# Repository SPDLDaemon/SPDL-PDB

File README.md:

# Smart Product Design Lab - Power Distribution Board v2.1
## features
* 16 JST XH plugs with 3.3v ground and 5 volts
* 8 molex 254 plugs for servos

## user guide image

#### [link to user guide image](/218PDBguide.drawio.png)

### [link to schematic](/schematic.pdf)
#### [link to image of PCB traces](/pcb.pdf)
<!-- ### board explanation video coming soon -->

## assembly
### [assembly instructions](/assembly_instructions.md)

[Interactive BOM](/ibom.html) (download file and open in a browser)

<!-- ### assembly video coming soon -->

## current limits:
* board total: 16 amps (theoretical) ??? amps (tested), limited by the traces and main battery screw terminals
* 5-3: 2 amps (theoretical) ??? amps (tested), limited by the HW-411 buck voltage regulator
* 3.3-1 + 5-1: 1 amp (theoretical) ??? amps (tested), limited by the TLV761 linear voltage regulator
* 3.3-2 + 5-2: 1 amp (theoretical) ??? amps (tested), limited by the TLV761 linear voltage regulator

## images

## KiCAD Symbols
### [simple symbol](https://github.com/SPDLDaemon/SPDL-PDB/blob/main/pdb.kicad_sym)

### [detailed symbol](https://github.com/SPDLDaemon/SPDL-PDB/blob/main/pdb-detailed.kicad_sym)

## buying PCBs and components 
1x set of components from [bill of materials](/BOM.csv)

2x tamiya connectors for batteries (with wires)

1x main power switch (for example 141-RCA1913F1ABLKBLKWHT3-ND)

1x fuse holder (with wires) and fuse

1x PCB from ([gerber files](/gerbers.zip))

JST XH socket housings (16) 455-2219-ND

JST XH socket crimps (48) 455-1135-1000-ND

4 inches of 18 AWG wire

small flathead screwdriver

JST XH crimper

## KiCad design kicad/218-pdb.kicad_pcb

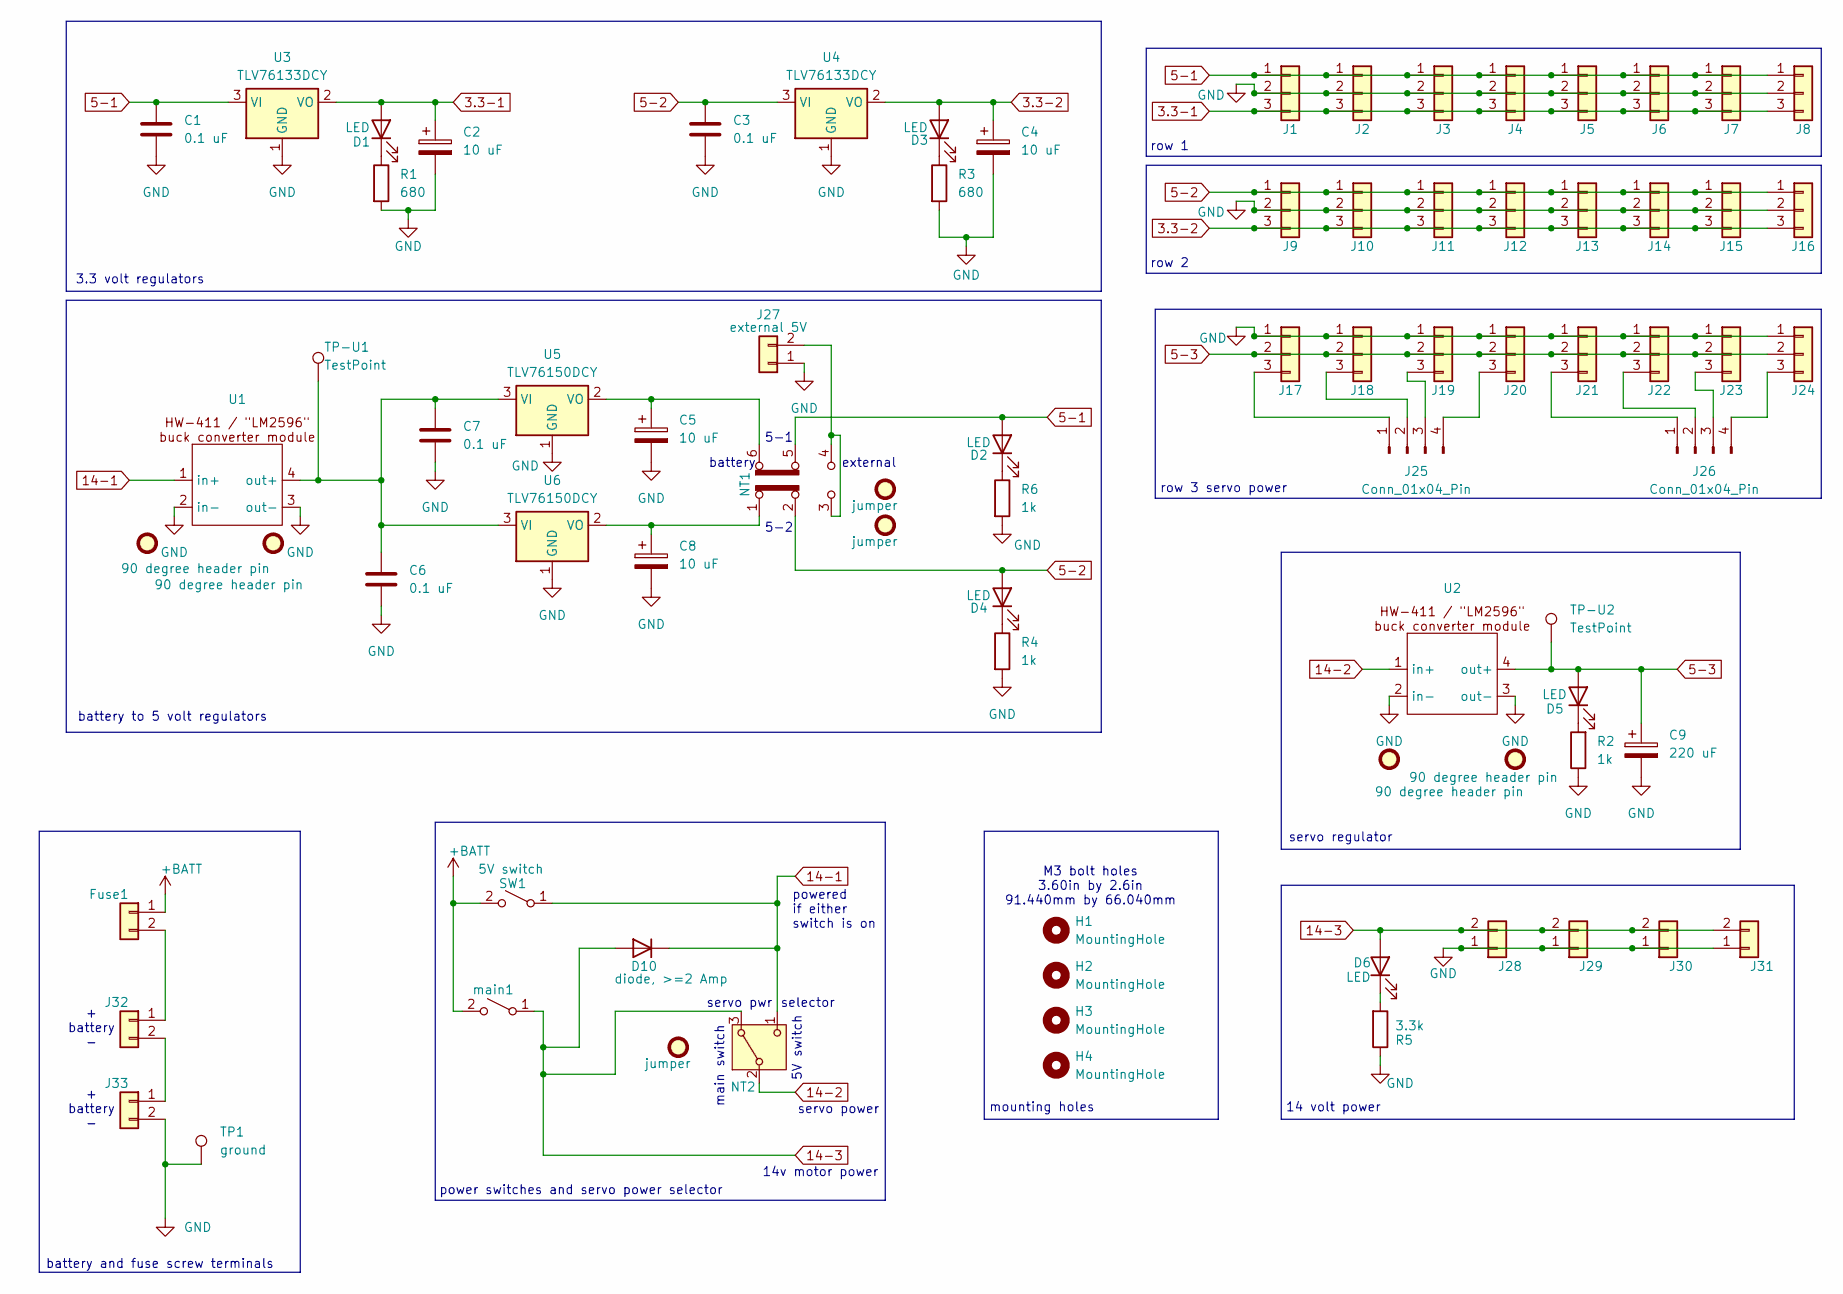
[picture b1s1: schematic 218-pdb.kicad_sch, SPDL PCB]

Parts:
C1, C3, C6, C7: 0.1 uF; C_Disc_D3.0mm_W2.0mm_P2.50mm; Part_Number 0.1 uF ceramic capacitor
C2, C4, C5, C8: 10 uF; C_Disc_D3.8mm_W2.6mm_P2.50mm; Part_Number 10uF tantalum (polarized) capacitor
C9: 220 uF; CP_Radial_D5.0mm_P2.50mm; Part_Number 220uf electrolytic
D1, D2, D3, D4, D5, D6: LED; LED_D3.0mm; Part_Number 3 mm diameter LED
D10: diode, >=2 Amp; D_DO-15_P2.54mm_Vertical_AnodeUp; Part_Number >=2 Amp diode, e.g. Diotec 1N5060
FID1, FID2, FID3, FID4: 90 degree header pin; PinHeader_1x01_P2.54mm_H; Part_Number 90 degree header pin
FID5, FID6, FID10: jumper; Part_Number pin jumper 0.1" pitch Sullins QPC02SXGN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
Fuse1: fuse; CUI_TB007-508-02BE; Part_Number screw terminal, 5.08" pitch, TB007-508-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
H1, H2, H3, H4: MountingHole; MountingHole_3.2mm_M3_ISO7380
J1, J2, J3, J4, J5, J6, J7, J8, J9, J10, J11, J12, J13, J14, J15, J16: Conn_01x03; JST_XH_B3B-XH-AM_1x03_P2.50mm_Vertical; Part_Number 3 pin JST XH
J17, J18, J19, J20, J21, J22, J23, J24: Conn_01x03; Molex_KK-254_AE-6410-03A_1x03_P2.54mm_Vertical; Part_Number 3 pin KK254 molex 0022232031
J25, J26: Conn_01x04_Pin; PinHeader_1x04_P2.54mm_Vertical; Part_Number 4 header pins 0.1" pitch
J27: external 5V; Molex_KK-254_AE-6410-02A_1x02_P2.54mm_Vertical; Part_Number 2 pin KK 254 molex 0022232021
J28, J29, J30, J31: 14v; CUI_TB007-508-02BE; Part_Number screw terminal, 5.08" pitch, TB007-508-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
J32, J33: battery; CUI_TB007-508-02BE; Part_Number screw terminal, 5.08" pitch, TB007-508-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
NT1: SW_Slide_DPDT; PinHeader_2x03_P2.54mm_Vertical; Part_Number 2x3 header pins
NT2: PinHeader_1x03_P2.54mm_Vertical; Part_Number 3 header pins 0.1" pitch
R1, R3: 680; R_Axial_DIN0309_L9.0mm_D3.2mm_P2.54mm_Vertical; Part_Number spdl; digikey_part_number n/a
R2, R4, R6: 1k; R_Axial_DIN0309_L9.0mm_D3.2mm_P2.54mm_Vertical; Part_Number spdl; digikey_part_number n/a
R5: 3.3k; R_Axial_DIN0309_L9.0mm_D3.2mm_P2.54mm_Vertical; Part_Number spdl; digikey_part_number n/a
SW1: 5V switch; 1101A4CQEA; Part_Number 1101A4CQEA; digikey_part_number 2449-1101A4CQEA-ND
TP1: ground; TestPoint_Bridge_Pitch5.08mm_Drill0.7mm; Part_Number piece of wire
TP-U1, TP-U2: TestPoint; TestPoint_THTPad_D2.0mm_Drill1.0mm
U1, U2: DC-DC buck; HW-411; Part_Number HW-411 lm2596 buck converter module; digikey_part_number n/a
U3, U4: TLV76133DCY; SOT-223-3_TabPin2; Part_Number TLV76133DCY
U5, U6: TLV76150DCY; SOT-223-3_TabPin2; Part_Number TLV76150DCY
main1: MainSW; CUI_TB007-508-02BE; Part_Number screw terminal, 5.08" pitch, TB007-508-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

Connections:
3.3-1: C2.1, D1.2 (A), J1.3, J2.3, J3.3, J4.3, J5.3, J6.3, J7.3, J8.3, U3.2 (VO)
3.3-2: C4.1, D3.2 (A), J9.3, J10.3, J11.3, J12.3, J13.3, J14.3, J15.3, J16.3, U4.2 (VO)
5-1: C1.1, D2.2 (A), J1.1, J2.1, J3.1, J4.1, J5.1, J6.1, J7.1, J8.1, NT1.5 (B), U3.3 (VI)
5-2: C3.1, D4.2 (A), J9.1, J10.1, J11.1, J12.1, J13.1, J14.1, J15.1, J16.1, NT1.2 (B), U4.3 (VI)
5-3: C9.1, D5.2 (A), J17.2, J18.2, J19.2, J20.2, J21.2, J22.2, J23.2, J24.2, TP-U2.1, U2.4 (out+)
14-1: D10.1 (K), NT2.1 (C), SW1.1 (A), U1.1 (in+)
14-2: NT2.2 (B), U2.1 (in+)
14-3: D6.2 (A), D10.2 (A), J28.2, J29.2, J30.2, J31.2, NT2.3 (A), main1.1 (A)
+BATT: Fuse1.1, SW1.2 (B), main1.2 (B)
GND: C1.2, C2.2, C3.2, C4.2, C5.2, C6.2, C7.2, C8.2, C9.2, J1.2, J2.2, J3.2, J4.2, J5.2, J6.2, J7.2, J8.2, J9.2, J10.2, J11.2, J12.2, J13.2, J14.2, J15.2, J16.2, J17.1, J18.1, J19.1, J20.1, J21.1, J22.1, J23.1, J24.1, J27.1, J28.1, J29.1, J30.1, J31.1, J33.2, R1.2, R2.1, R3.2, R4.2, R5.1, R6.2, TP1.1, U1.2 (in-), U1.3 (out-), U2.2 (in-), U2.3 (out-), U3.1 (GND), U4.1 (GND), U5.1 (GND), U6.1 (GND)
unnamed: D1.1 (K), R1.1
unnamed: D2.1 (K), R6.1
unnamed: D3.1 (K), R3.1
unnamed: D4.1 (K), R4.1
unnamed: D5.1 (K), R2.2
unnamed: D6.1 (K), R5.2
unnamed: Fuse1.2, J32.1
unnamed: J17.3, J25.1
unnamed: J18.3, J25.2
unnamed: J19.3, J25.3
unnamed: J20.3, J25.4
unnamed: J21.3, J26.1
unnamed: J22.3, J26.2
unnamed: J23.3, J26.3
unnamed: J24.3, J26.4
unnamed: J27.2, NT1.3 (C), NT1.4 (A)
unnamed: J32.2, J33.1
unnamed: C6.1, C7.1, TP-U1.1, U1.4 (out+), U5.3 (VI), U6.3 (VI)
unnamed: C5.1, NT1.6 (C), U5.2 (VO)
unnamed: C8.1, NT1.1 (A), U6.2 (VO)

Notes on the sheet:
battery to 5 volt regulators
mounting holes
battery
battery and fuse screw terminals
selector
external
+ battery -
row 1
M3 bolt holes 3.60in by 2.6in 91.440mm by 66.040mm
servo regulator
row 2
3.3 volt regulators
power switches and servo power selector
5-1
servo pwr
5-2
row 3 servo power
5V switch
powered if either switch is on
main switch
14 volt power
14v motor power
servo power

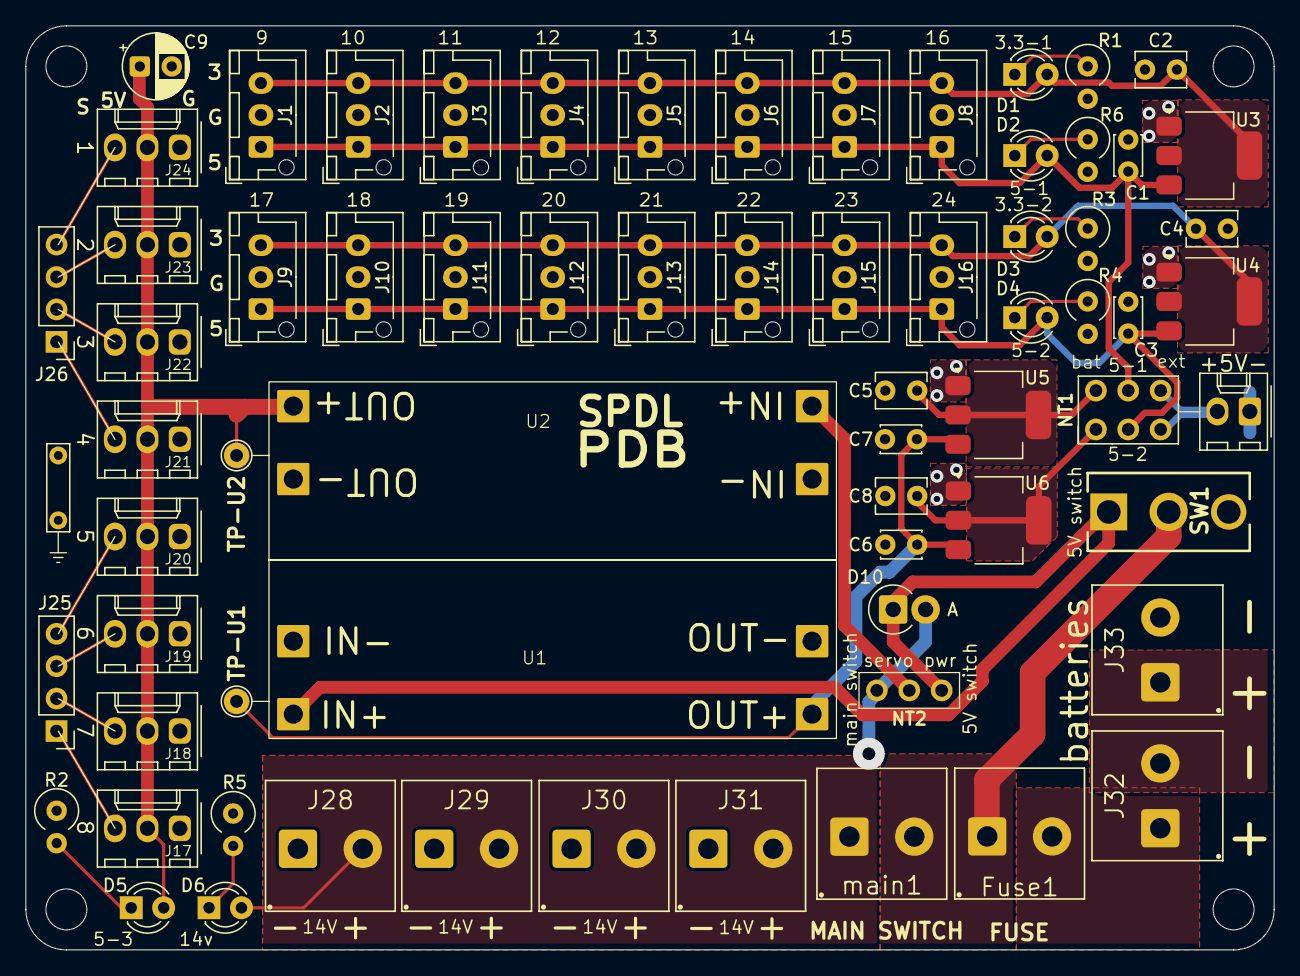
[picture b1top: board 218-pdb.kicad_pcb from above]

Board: 2 copper layers, 97.8 x 72.4 mm, 80 parts (0 on the bottom side), 30 nets.

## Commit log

2026-01-01 edit silkscreen
2026-01-01 align
2026-01-01 align silkscreen
2026-01-02 update BOM, silkscreen
2026-01-02 BOT process kicad
2026-01-02 update image
2026-01-03 update bom
2026-01-03 change diode
2026-01-04 start diagram
2026-01-07 update silkscreen
2026-01-07 edit diagram
2026-01-07 update diagram
2026-01-14 update presentation
2026-01-15 restart
2026-01-17 start design E
2026-01-19 change schematic and start layout
2026-01-19 edit switch
2026-01-19 add traces
2026-01-22 Update README with minor formatting changes
2026-01-22 adjust layout
2026-01-22 work on diagram and silkscreen
2026-01-26 align silkscreen and edit diagram
2026-01-29 add fuse terminal
2026-01-29 align silkscreen and comment schematic
2026-01-29 change jst xh model
2026-01-29 advice from Karl
2026-02-07 assembly instructions in progress
2026-02-11 add photos
2026-02-12 Update README with KiCAD symbols section
    Added KiCAD symbols section with links to simple and detailed symbols.
2026-02-12 add images
2026-02-12 add 5v switch to symbol
2026-02-14 add assembly picture
2026-02-14 add note about batteries
2026-02-14 add testing to assembly instructions
2026-02-15 correct errors in assembly instructions, thanks Gus!
2026-02-17 add note about screw terminals
2026-02-17 add note about tinned fuse holder ends
2026-02-19 add note about regulators looking similar
2026-02-19 label external 5v plug
2026-05-02 add ibom
